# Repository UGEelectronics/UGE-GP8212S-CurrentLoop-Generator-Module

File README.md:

# UGE GP8212S 4–20 mA Current Loop Generator Module

Compact **I²C-controlled** analog output board based on the Linearin **GP8212S-TC50-EW** (15-bit DAC → industrial **0 / 4–20 mA** current loop).

**[Open interactive BOM ↗](https://ugeelectronics.github.io/UGE-GP8212S-CurrentLoop-Generator-Module/GP8212SBOM.html)** — browser BOM for soldering / identifying parts (do not use the GitHub `.html` file viewer).

| | |
|---|---|
| **Chip** | GP8212S-TC50-EW (ESOP-8), 15-bit I²C |
| **Output** | 0–25 mA full scale (typical with Rs = 100 Ω); use 4–20 mA for industrial loops |
| **Interface** | I²C address **0x58**, logic **2.7–5.5 V** (Arduino & ESP32 friendly) |
| **Module power** | **5 V** input → onboard **MT3608** boost → ~**12 V** for the DAC |
| **MCU examples** | Arduino / ESP32 library in this repo; STM32 bit-bang reference included |
| **Interactive BOM** | **[Open in browser](https://ugeelectronics.github.io/UGE-GP8212S-CurrentLoop-Generator-Module/GP8212SBOM.html)** |
| **Buy the full module** | **[uge-one.com](https://uge-one.com/product/gp8212s-4-20-ma-current-loop-generator-transmitter-i2c-module/)** |

---

## Buy

| Item | Link |
|------|------|
| **Full module (assembled)** | [uge-one.com — GP8212S 4–20 mA I2C module](https://uge-one.com/product/gp8212s-4-20-ma-current-loop-generator-transmitter-i2c-module/) |
| **GP8212S chip only** | [uge-one.com — GP8212S-TC50-EW](https://uge-one.com/product/gp8212s-tc50-ew-15-bit-i%c2%b2c-to-4-20ma-dac-ic-esop-8/) |
| **Empty bare PCB** | [uge-one.com — PCB for I2C 4–20 mA generator](https://uge-one.com/product/pcb-for-i2c-4-20ma-generator-module/) |
| **Interactive BOM** | **[Open live BOM](https://ugeelectronics.github.io/UGE-GP8212S-CurrentLoop-Generator-Module/GP8212SBOM.html)** |

SKU of the full module: **GP8212S-MOD**. More products: [UGE Electronics](https://uge-one.com/).

---

## Repository layout

```text
software/GP8212S/     Arduino & ESP32 library + examples
docs/                 GitHub Pages site + interactive BOM + images
hardware/             Link to the live BOM (GitHub code view cannot render HTML)
stm32_reference/      Original STM32F10x bit-bang I²C (MyI2C)
```

---

## Quick start (Arduino / ESP32)

### 1. Install the library

**Option A — manual**

1. Download this repository (Code → Download ZIP) or clone it.
2. Copy the folder `software/GP8212S` into your Arduino libraries directory:
   - Windows: `Documents\Arduino\libraries\GP8212S`
   - macOS: `~/Documents/Arduino/libraries/GP8212S`
   - Linux: `~/Arduino/libraries/GP8212S`
3. Restart the Arduino IDE.

**Option B — ZIP**

Sketch → Include Library → Add .ZIP Library… and select a ZIP that contains the `GP8212S` folder (with `library.properties` at its root).

### 2. Wire the module

| Module | Arduino Uno / Nano | ESP32 (typical) | Notes |
|--------|--------------------|-----------------|-------|
| **5 V** (H1) | 5 V | 5 V-capable supply | Powers MT3608 → ~12 V for the DAC |
| **GND** (H1) | GND | GND | Common ground |
| **SCL** (H2) | A5 | GPIO 22 | I²C clock |
| **SDA** (H2) | A4 | GPIO 21 | I²C data |
| **IOUT** (blue terminal) | — | — | Loop output — connect load / meter here |

- Share **GND** between MCU and module.
- Do **not** feed the GP8212S chip `VCC` pin from USB 5 V directly — use the module’s **5 V** input so the MT3608 can boost to ~12 V.
- I²C works at **3.3 V** (ESP32) or **5 V** (classic Arduino).

### 3. Minimal sketch

```cpp
#include <Wire.h>
#include <GP8212S.h>

GP8212S dac;  // I2C 0x58, 25 mA full scale (Rs = 100 Ω)

void setup() {
  Serial.begin(115200);

#if defined(ESP32)
  if (dac.begin(21, 22) != 0) {   // SDA, SCL
#else
  if (dac.begin() != 0) {
#endif
    Serial.println("GP8212S not found");
    while (true) {}
  }

  dac.setCurrent_mA(12.0);     // milliamps
  // After one-time calibration, paste your line from "apply":
  // dac.calibrate4_20(5200, 26200);
  // dac.setPercent4_20(50);   // 0–100% of 4–20 mA span
  // dac.setDAC(0x3D70);       // raw 15-bit code
}

void loop() {}
```

### 4. Examples

After install: **File → Examples → GP8212S**

| Example | What it does |
|---------|----------------|
| **CurrentSweep** | Sweeps 4 → 20 → 4 mA |
| **SetAndStore** | Set mA from Serial; optional NVM `store()` |
| **Calibrate4_20** | Interactive two-point calibration with a meter |

---

## API overview

| Method | Description |
|--------|-------------|
| `begin(sda, scl, freq)` | Init I²C and probe (returns `0` on ACK) |
| `setCurrent_mA(mA)` | Output current in mA (0 … full scale) |
| `setPercent4_20(pct)` | 0% → 4 mA, 100% → 20 mA |
| `setDAC(code)` | Raw 15-bit code `0 … 0x7FFF` |
| `calibrate4_20(dac4, dac20)` | Use measured codes for accurate 4–20 mA |
| `store(sda, scl)` | Save last DAC value in chip NVM (survives power-off) |

Ideal codes with **Rs = 100 Ω** (0–25 mA full scale):

| Current | Approx. DAC |
|---------|-------------|
| 4 mA | 5243 (`0x147A`) |
| 12 mA | 15728 (`0x3D70`) |
| 20 mA | 26214 (`0x6666`) |
| 25 mA | 32767 (`0x7FFF`) |

Datasheet: `IOUT = (2.5 V / Rs) × (DATA / 0x7FFF)`.

---

## Calibration (recommended — once per board)

You do **not** repeat this on every power-on. Run it once, then paste `dac.calibrate4_20(...)` into your sketches.

### What you need

- Arduino (or ESP32) + this module wired as above  
- **~330 Ω** load on the blue **IOUT** terminal (**1 W preferred**)  
- DMM measuring the **actual loop current** through that resistor  

### Steps

1. Upload **Examples → GP8212S → Calibrate4_20**.
2. Open **Serial Monitor** at **115200** (line ending: **Newline**).
3. Type **`4`**  
   Read the meter (example: **8.08 mA**).  
   Type **`M 8.08`** — the sketch rescales to 4 mA and **auto-saves** the 4 mA point.
4. Type **`20`**  
   Read the meter (example: **25.63 mA**).  
   Type **`M 25.63`** — rescales to 20 mA and **auto-saves** the 20 mA point.
5. Type **`apply`**. You get a line like:

```cpp
dac.calibrate4_20(5200, 26200);
```

6. Put that line in `setup()` **after** `dac.begin(...)` in all future code for this board.

Optional fine trim before `apply`: `+++` `---` (±2000), `++` `--` (±500), `+` `-` (±50), `]` `[` (±5). Commands are case-insensitive (`m` / `M`).
---

## Hardware & soldering

### Interactive BOM (opens in the browser)

GitHub’s file viewer only shows HTML **source**. Use one of these instead:

| | |
|---|---|
| **Live page (recommended)** | [Open interactive BOM](https://ugeelectronics.github.io/UGE-GP8212S-CurrentLoop-Generator-Module/GP8212SBOM.html) |
| **Docs home** | [ugeelectronics.github.io/…/](https://ugeelectronics.github.io/UGE-GP8212S-CurrentLoop-Generator-Module/) |
| **Offline** | Download [`docs/GP8212SBOM.html`](docs/GP8212SBOM.html) and double-click it |

> **First-time Pages setup (repo admins) — required once:**  
> 1. Open **Settings → Pages**  
> 2. Under **Build and deployment → Source**, choose **Deploy from a branch**  
> 3. Branch: **main**, folder: **/docs** → **Save**  
> 4. Wait about a minute, then open the live BOM link above.

---

## STM32 reference

[`stm32_reference/MyI2C.c`](stm32_reference/MyI2C.c) is the original **STM32F10x open-drain bit-bang I²C** layer (no high-level DAC API). The Arduino library replaces that with `Wire` and implements the GP8212S register write / store sequence.

---

## Notes & limits

- Default I²C address: **`0x58`**.
- Chip `VCC` range per datasheet: **9–36 V**; this module uses ~**12 V** from MT3608 after **5 V** input.
- Max load resistance shrinks at 12 V vs 24 V — keep calibration / field loads in the **~220–330 Ω** range unless you raise the boost voltage within safe design limits.
- There is **no official Arduino library named GP8212S** from the chip vendor; DFRobot’s [GP8XXX](https://github.com/DFRobot/DFRobot_GP8XXX) covers related parts (e.g. GP8211S / GP8302) but not this module. Use **UGE `GP8212S`** here.

---

## License

MIT — see [LICENSE](LICENSE).  
© 2026 UGE Electronics — [uge-one.com](https://uge-one.com/)

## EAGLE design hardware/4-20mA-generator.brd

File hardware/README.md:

# Hardware

The interactive BOM is published as a **live web page** (GitHub does not render `.html` files in the code viewer).

**Open here:**  
https://ugeelectronics.github.io/UGE-GP8212S-CurrentLoop-Generator-Module/GP8212SBOM.html

Source file in this repo: [`docs/GP8212SBOM.html`](../docs/GP8212SBOM.html)  
(You can also download that file and open it locally in any browser.)

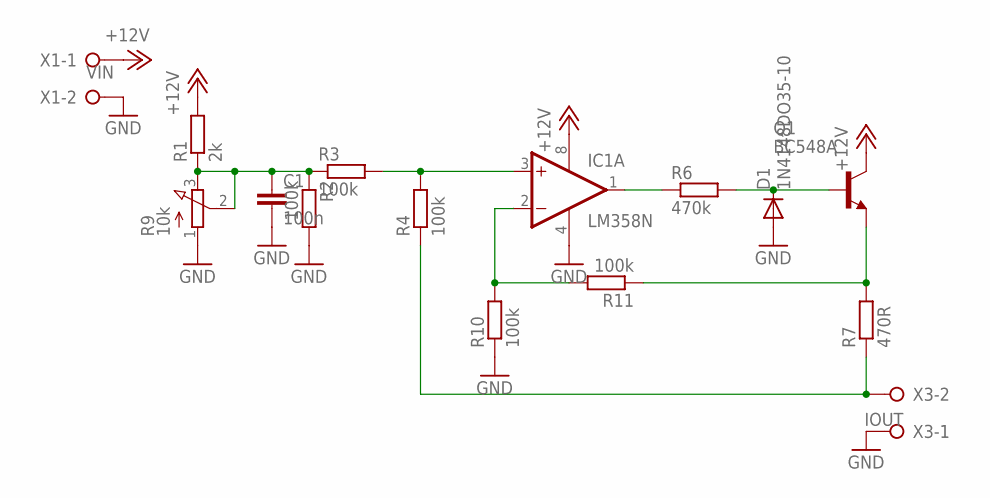
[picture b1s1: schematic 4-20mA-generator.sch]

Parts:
C1: 100n; C050-024X044
D1: 1N4148DO35-10; DO35-10
IC1: LM358N; DIL08
Q1: BC548A; TO92-EBC
R1: 2k; 0207/7
R2, R3, R4, R10, R11: 100k; 0207/7
R6: 470k; 0207/7
R7: 470R; 0207/7
R9: 10k; 3RP/1610N
X1: VIN; W237-132
X3: IOUT; W237-132

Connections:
+12V: IC1.8 (V+), Q1.C, R1.2, X1.1
GND: C1.2, D1.A, IC1.4 (V-), R2.2, R9.1 (A), R10.1, X1.2, X3.1
unnamed: C1.1, R1.1, R2.1, R3.1, R9.2 (S), R9.3 (E)
unnamed: IC1.2 (-IN), R10.2, R11.2
unnamed: IC1.1 (OUT), R6.1
unnamed: D1.C, Q1.B, R6.2
unnamed: Q1.E, R7.2, R11.1
unnamed: R4.1, R7.1, X3.2
unnamed: IC1.3 (+IN), R3.2, R4.2

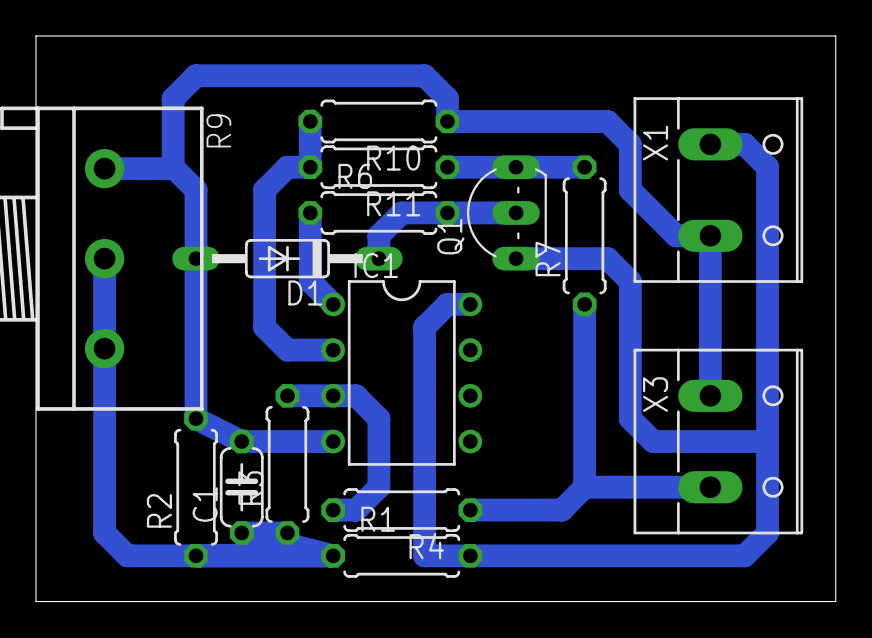
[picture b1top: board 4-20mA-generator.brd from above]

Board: 2 copper layers, 44.4 x 31.4 mm, 15 parts (0 on the bottom side), 9 nets.
